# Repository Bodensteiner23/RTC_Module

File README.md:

# RTC Module PCF8563T
RTC module which is based on the Arduino template but has modified components (RTC PCF8563T) and is designed for ordering from JLCPCB.

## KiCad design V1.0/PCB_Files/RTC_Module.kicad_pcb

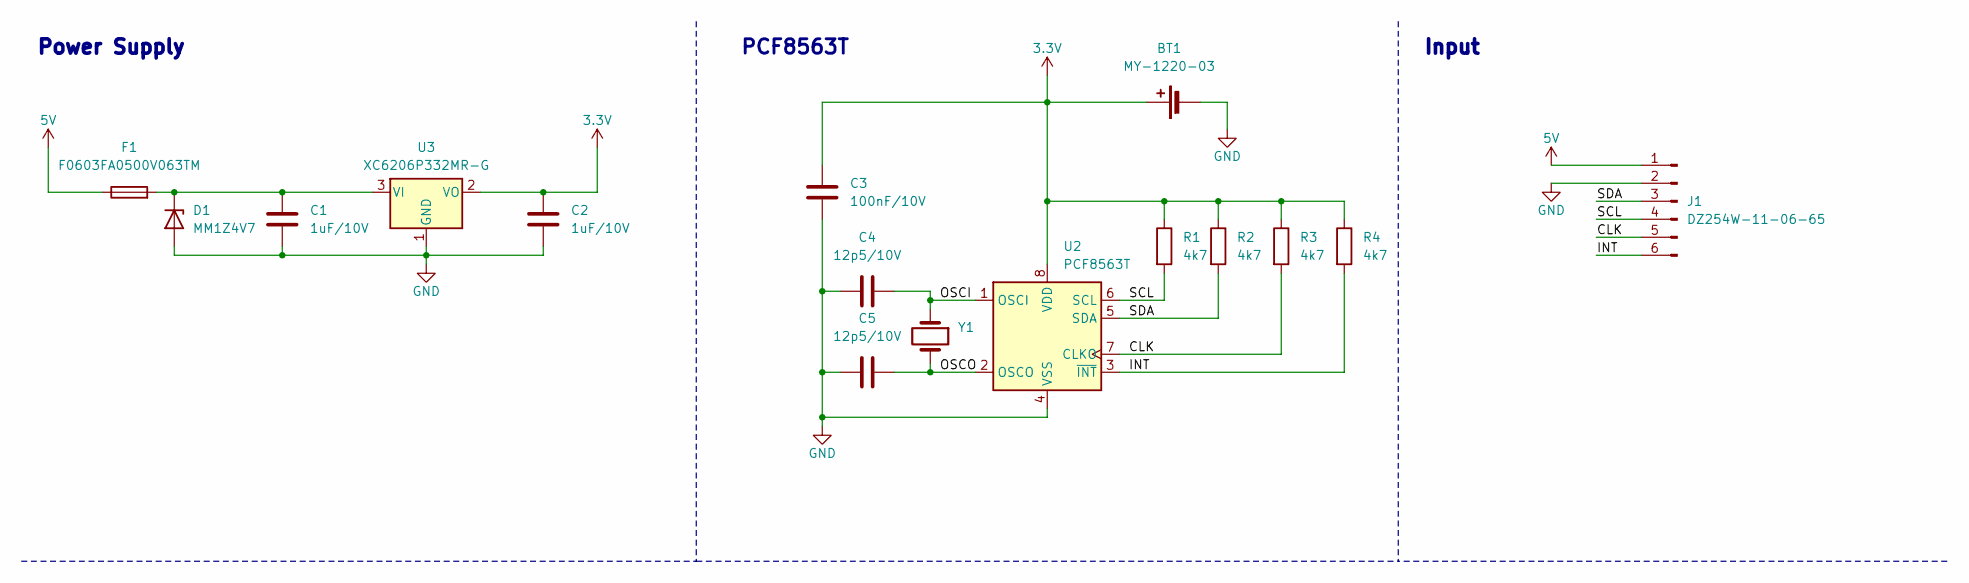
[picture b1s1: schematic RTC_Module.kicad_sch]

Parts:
BT1: MY-1220-03; BatteryHolder_LINX_BAT-HLD-012-SMT
C1, C2: 1uF/10V; C_0805_2012Metric
C3: 100nF/10V; C_0603_1608Metric
C4, C5: 12p5/10V; C_0603_1608Metric
D1: MM1Z4V7; D_SOD-123
F1: F0603FA0500V063TM; R_0603_1608Metric
J1: DZ254W-11-06-65; PinHeader_1x06_P2.54mm_Horizontal
R1, R2, R3, R4: 4k7; R_0603_1608Metric
U2: PCF8563T; SOIC-8_3.9x4.9mm_P1.27mm
U3: XC6206P332MR-G; SOT-23-3
Y1: Q13FC13500004; Crystal_SMD_MicroCrystal_CC7V-T1A-2Pin_3.2x1.5mm

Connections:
3.3V: BT1.1 (+), C2.1, C3.1, R1.1, R2.1, R3.1, R4.1, U2.8 (VDD), U3.2 (VO)
5V: F1.1, J1.1
/CLK: J1.5, R3.2, U2.7 (CLKO)
/INT: J1.6, R4.2, U2.3 (~INT)
/OSCI: C4.1, U2.1 (OSCI), Y1.1
/OSCO: C5.1, U2.2 (OSCO), Y1.2
/SCL: J1.4, R1.2, U2.6 (SCL)
/SDA: J1.3, R2.2, U2.5 (SDA)
GND: BT1.2 (-), C1.2, C2.2, C3.2, C4.2, C5.2, D1.2 (A), J1.2, U2.4 (VSS), U3.1 (GND)
unnamed: C1.1, D1.1 (K), F1.2, U3.3 (VI)

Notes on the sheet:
Power Supply
PCF8563T
Input

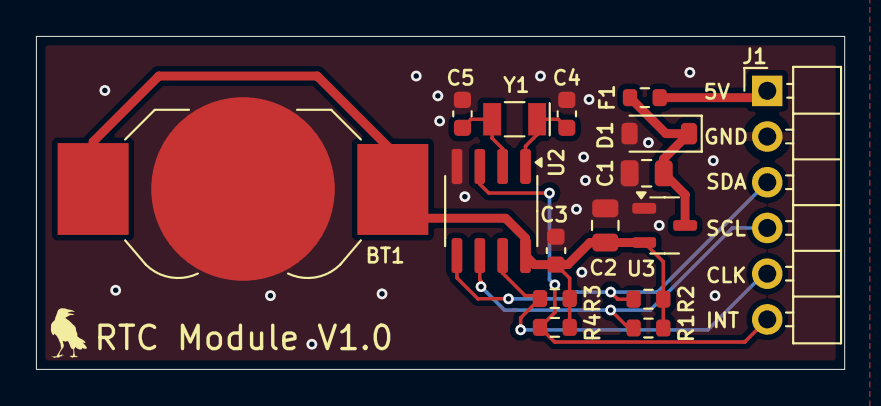
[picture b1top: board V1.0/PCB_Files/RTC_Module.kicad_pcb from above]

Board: 2 copper layers, 44.9 x 18.5 mm, 16 parts (0 on the bottom side), 10 nets.

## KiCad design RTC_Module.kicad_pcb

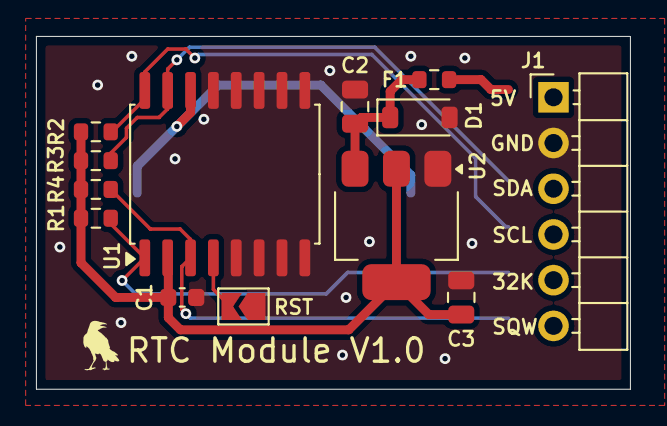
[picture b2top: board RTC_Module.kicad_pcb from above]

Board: 2 copper layers, 33.0 x 19.6 mm, 14 parts (1 on the bottom side), 10 nets.

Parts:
BT1: Battery_Cell; BatteryHolder_LINX_BAT-HLD-012-SMT
C1: 100n/10V; C_0603_1608Metric
C2: 10uF/10V; C_0805_2012Metric
C3: 22uF/10V; C_0805_2012Metric
D1: MM1Z4V7; D_SOD-123
F1: F0603FA0500V063TM; R_0603_1608Metric
J1: DZ254W-11-06-65; PinHeader_1x06_P2.54mm_Horizontal
JP1: SolderJumper_2_Open; SolderJumper-2_P1.3mm_Open_TrianglePad1.0x1.5mm
R1, R2, R3, R4: 4k7; R_0603_1608Metric
U1: DS3231SN#T&R; SOIC-16W_7.5x10.3mm_P1.27mm
U2: AMS1117-3.3; SOT-223-3_TabPin2

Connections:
3.3V: C1.1, C3.1, R1.1, R2.1, R3.1, R4.1, U1.2 (VCC), U2.2 (VO)
5V: F1.1, J1.1
/32KHZ: J1.5, R1.2, U1.1 (32KHZ)
/RST: JP1.2 (B), U1.4 (~RST)
/SCL: J1.4, R2.2, U1.16 (SCL)
/SDA: J1.3, R3.2, U1.15 (SDA)
/SQW: J1.6, R4.2, U1.3 (~INT/SQW)
GND: BT1.2 (-), C1.2, C2.2, C3.2, D1.2 (A), J1.2, JP1.1 (A), U1.5 (GND), U1.6 (GND), U1.7 (GND), U1.8 (GND), U1.9 (GND), U1.10 (GND), U1.11 (GND), U1.12 (GND), U1.13 (GND), U2.1 (GND)
unnamed: BT1.1 (+), U1.14 (VBAT)
unnamed: C2.1, D1.1 (K), F1.2, U2.3 (VI)

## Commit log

2024-07-28 Initall Commit of Porject.
2024-07-28 Moved to Another dir.
2024-07-28 Added new RTC that is much cheaper.
2024-07-28 Changed gitignore.
2024-07-28 Deleted files
2024-07-28 Changed gitognore.
2024-07-28 Changed gitignore again
2024-07-29 Just test change in schematic.
2024-07-29 Continues with layout
2024-07-29 Finished PCB with new RTC.
2024-07-29 Updated gitignore.
2024-07-29 Added step of DCDC. Updated gitignore. Now version with battery cell on top side.
2024-07-29 Finished with only Top Side Components.
2024-07-29 Now finished and choose SMD battery.
2024-07-29 This is ordered Version!!!!
2024-07-30 Added V1 dir and placed all files in it.
2024-07-30 This is ordered Version!!!
2024-07-30 Changed Readme and added png.
2024-07-30 Updated md.
2024-07-30 Added Schematic Pdf.
2024-07-30 Just downloaded some Package.
